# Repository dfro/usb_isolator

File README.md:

# usb_isolator
This is KiCAD project for USB isolator based on ADuM4160 and ADuM6000

##Features
- Current limiting (about 80mA) and overcurrent indication
- USB powered

## License
This project licensed under CC0 1.0

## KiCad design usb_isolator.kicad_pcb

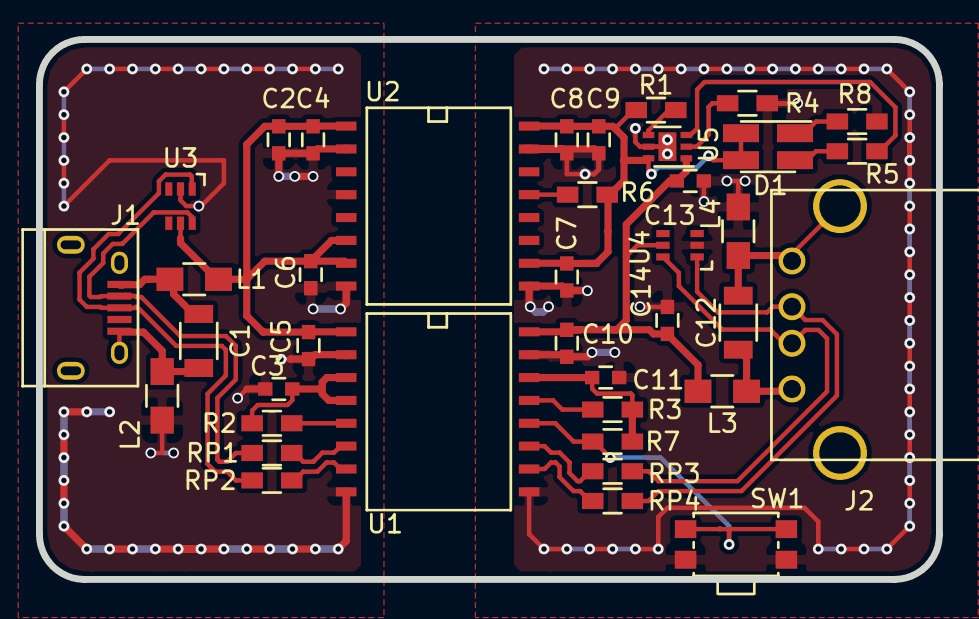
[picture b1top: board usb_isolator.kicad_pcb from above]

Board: 2 copper layers, 50.0 x 30.0 mm, 39 parts (0 on the bottom side), 28 nets.

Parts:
C1, C12: 0.1uF; C_1206
C2, C6, C7, C9: 10uF; C_0603
C3, C4, C5, C8, C10, C11: 0.1uF; C_0603
C13: 22uF; C_0603
C14: 100uF; C_0603
D1: LED_Bi-Color; LED_Bi-Color_3.05x2.62mm
J1: USB-MICRO-B; USB_Micro-B
J2: USB; USB_A
L1, L2, L3, L4: INDUCTOR; R_0805_HandSoldering
R1, R6, R7: 40K; R_0603_HandSoldering
R2, R3: 10k; R_0603_HandSoldering
R4: 650k; R_0603_HandSoldering
R5: 270; R_0603_HandSoldering
R8: 1k; R_0603_HandSoldering
RP1, RP2, RP3, RP4: 24; R_0603_HandSoldering
SW1: SW_PUSH; SW_SPST_TL1014A
U1: ADuM4160; SO-16-W
U2: ADuM6000; SO-16-W
U3, U4: NUP4202; SC-70-6
U5: TPS25200; DFN-6-1EP_2x2mm_Pitch0.65mm

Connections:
/DD_OUT+: RP4.2, U1.10
/DD_OUT-: RP3.2, U1.11
/GNDA_OUT: C12.2, J2.4, J2.5, J2.6, L4.2
/GND_IN: C1.2, J1.5, J1.6, L2.1
/UD_IN+: RP2.1, U1.7
/UD_IN-: RP1.1, U1.6
/V_BUS_IN: C1.1, J1.1, L1.1
/V_ISO_OUT: C12.1, J2.1, L3.2
/V_ISO_UNPR: C7.1, C8.1, C9.1, D1.2, D1.4, R1.2, R6.1, U2.10, U2.16, U5.6
DD+: J2.3, RP4.1, U4.1
DD-: J2.2, RP3.1, U4.6
GND: C2.2, C3.2, C4.2, C5.2, C6.2, L2.2, U1.2, U1.8, U2.2, U2.4, U2.8, U3.2
GNDA: C7.2, C8.2, C9.2, C10.2, C11.2, C13.2, C14.2, L4.1, R4.1, R8.1, SW1.2, U1.9, U1.15, U2.9, U2.15, U4.2, U5.5, U5.7
unnamed: D1.1, R8.2
unnamed: D1.3, R5.2
unnamed: R1.1, U5.4
unnamed: R2.1, U1.5
unnamed: R3.2, U1.13
unnamed: R4.2, U5.2
unnamed: R5.1, U5.3
unnamed: R6.2, U2.13
PIN: R7.1, SW1.1, U1.12
UD+: J1.3, RP2.2, U3.1
UD-: J1.2, RP1.2, U3.6
VDD1: C3.1, R2.2, U1.3, U1.4
VDD2: C11.1, R3.1, R7.2, U1.14
V_BUS: C2.1, C4.1, C5.1, C6.1, L1.2, U1.1, U2.1, U2.6, U2.7, U3.5
V_ISO: C10.1, C13.1, C14.1, L3.1, U1.16, U4.5, U5.1
